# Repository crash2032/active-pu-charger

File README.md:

# Rechargeable Power Board for Active Guitar Pickups

Open-source, rechargeable 9 V supply for active pickups (EMG, Fishman Fluence, Seymour Duncan Blackouts and similar).
It replaces the 9 V battery: a single Li-ion/LiPo cell is charged from USB-C 5 V, boosted, heavily filtered and regulated to a clean **9.0 V**.
The board switches itself on only when a cable is plugged into the guitar (stereo jack, ring contact), and a single bi-color LED shows the charge state — the same behaviour as the Fishman rechargeable pack.

Originally based on the [freestompboxes.org thread](https://www.freestompboxes.org/viewtopic.php?t=32759); **v3** is a full redesign: smaller, lower idle current, all parts on one side, ready for turnkey assembly.

| Top (components) | Bottom |
|---|---|
|  |  |

## Specifications

| | |
|---|---|
| Board | 31 × 19 mm, 2 layers, 1.6 mm, all SMD parts on top |
| Battery | 1 × Li-ion / LiPo (18650, pouch 1200 mAh, …) **with its own protection (BMS)** |
| Charging | TP4057, 5 V from USB-C, 500 mA (Rprog = 2 kΩ) |
| Output | **9.02 V**, regulated, independent of load |
| Output noise | boost → RC (340 Hz) → capacitance multiplier (<1 Hz) → TPS7A4901 ultra-low-noise LDO (15 µV<sub>RMS</sub>, ≥52 dB PSRR to 400 kHz) |
| On/off | automatic via stereo-jack ring (ring = GND when a cable is plugged in) |
| Standby current (cable unplugged) | a few µA (charger leakage + capacitor leakage only) |
| Low-battery warning | red LED blinks below ~3.45 V (≈10–15 % left), blinking gets faster as the cell empties |

### LED indication (D3, one red/green LED)

| State | Red | Green |
|---|---|---|
| Charging | on | – |
| Fully charged | – | on |
| Playing, battery OK | – | – |
| Playing, battery low (< 3.45 V) | **blinking** | – |

## Wiring

All connections are 2.54 mm solder pads (no headers fitted). Labels are printed on the bottom silkscreen.

| Pad | Connect to |
|---|---|
| J3 `5V IN` / `GND` | USB-C charging socket in the guitar (VBUS / GND) |
| J2 `BAT+` / `GND` | battery (+ / −) — the cell **must** have its own BMS |
| J1 `+9V` | pickups / preamp +9 V (replaces the 9 V battery red wire) |
| J1 `GND` | pickups ground / output jack sleeve |
| J1 `RING` | output jack **ring** (stereo jack). Plugging a mono cable shorts ring to sleeve and turns the supply on |

> **USB-C note:** the USB-C socket in the guitar needs 5.1 kΩ pull-downs on CC1 and CC2, otherwise USB-C ↔ USB-C chargers will not supply 5 V.

## How it works

1. **Charger** – TP4057 linear charger (500 mA). STDBY drives the green LED directly (USB-powered); CHRG switches the battery-powered red LED through Q9/Q8, so the charger pins never see battery voltage when USB is unplugged.
2. **Switch-on** – Q7 is turned on by the jack ring; its collector (`VSW`) enables the boost converter and the low-battery detector. R22 holds EN low when unplugged.
3. **Boost** – TPS61041, 11.5 V (R7/R8). Q2 disconnects the output when the boost is off, so nothing drains the cell through the inductor/diode.
4. **Filtering & regulation** – R23/C2 RC filter → Q6 capacitance multiplier (R1/C3) → TPS7A4901 LDO set to 9.02 V by R26/R27 (C21 noise-reduction, C22 feed-forward).
5. **Low-battery blinker** – TLV3012 nanopower comparator with internal 1.242 V reference, wired as a relaxation oscillator that only runs below the threshold (~5 µA, only while a cable is plugged in).

## Repository layout

```
rechargeble_pack.kicad_pro / .kicad_sch / .kicad_pcb   KiCad 9 project
active_pu.kicad_sym, sym-lib-table                     project symbol library (TP4057, TLV3012, TPS7A4901, dual LED)
production/
  active-pu-charger-v3-gerbers.zip                     Gerbers + Excellon drill
  BOM-JLC.csv, CPL-JLC.csv                             JLCPCB assembly (LCSC part numbers)
  BOM-PCBWay.xlsx / .csv, CPL-PCBWay.csv               PCBWay / other turnkey assemblers (manufacturer + MPN)
docs/                                                  preview images
```

## Ordering

1. Upload `production/active-pu-charger-v3-gerbers.zip` (2 layers, 1.6 mm, any finish; min track/space 0.2/0.15 mm, min drill 0.3 mm).
2. For assembly upload the matching BOM + CPL. **Check component rotation in the assembler's placement preview** (SOT-23 and diodes are often offset by 90°/180° between KiCad and the assembler).
3. J1–J3 are wire pads — do not populate.
4. U4 (TPS7A4901) has an exposed thermal pad — it must be soldered (reflow / hot plate).

Before regenerating fabrication files after any edit: open the board in KiCad, press **B** (refill zones) and run **Inspect → Design Rules Checker**.

Notes:
- D3 (Lite-On LTST-C295KGKRKT) has no 3D model in the KiCad library, so it is not shown in the 3D viewer.
- Silkscreen reference designators are kept on the Fab layer (0402 parts are too small for the 1 mm minimum silkscreen text).

## Contacts

Designed by **[Abyss Sound Studio](https://abyss-prod.com/)** — mixing, mastering, video and photo for rock & metal musicians.

- Website: [abyss-prod.com](https://abyss-prod.com/)
- Instagram: [@abyss.sound.studio](https://www.instagram.com/abyss.sound.studio/) (best way to get in touch)
- YouTube: [@AbyssSoundStudio](https://www.youtube.com/@AbyssSoundStudio)
- Facebook: [abyss.sound.studio](https://www.facebook.com/abyss.sound.studio)
- SoundCloud: [abyss-sound-studio](https://soundcloud.com/abyss-sound-studio/sets/our-work)

Questions, bugs and improvements for this board: open an issue or pull request on GitHub.

## Contributing

Contributions are welcome — fork the repo and open a pull request.

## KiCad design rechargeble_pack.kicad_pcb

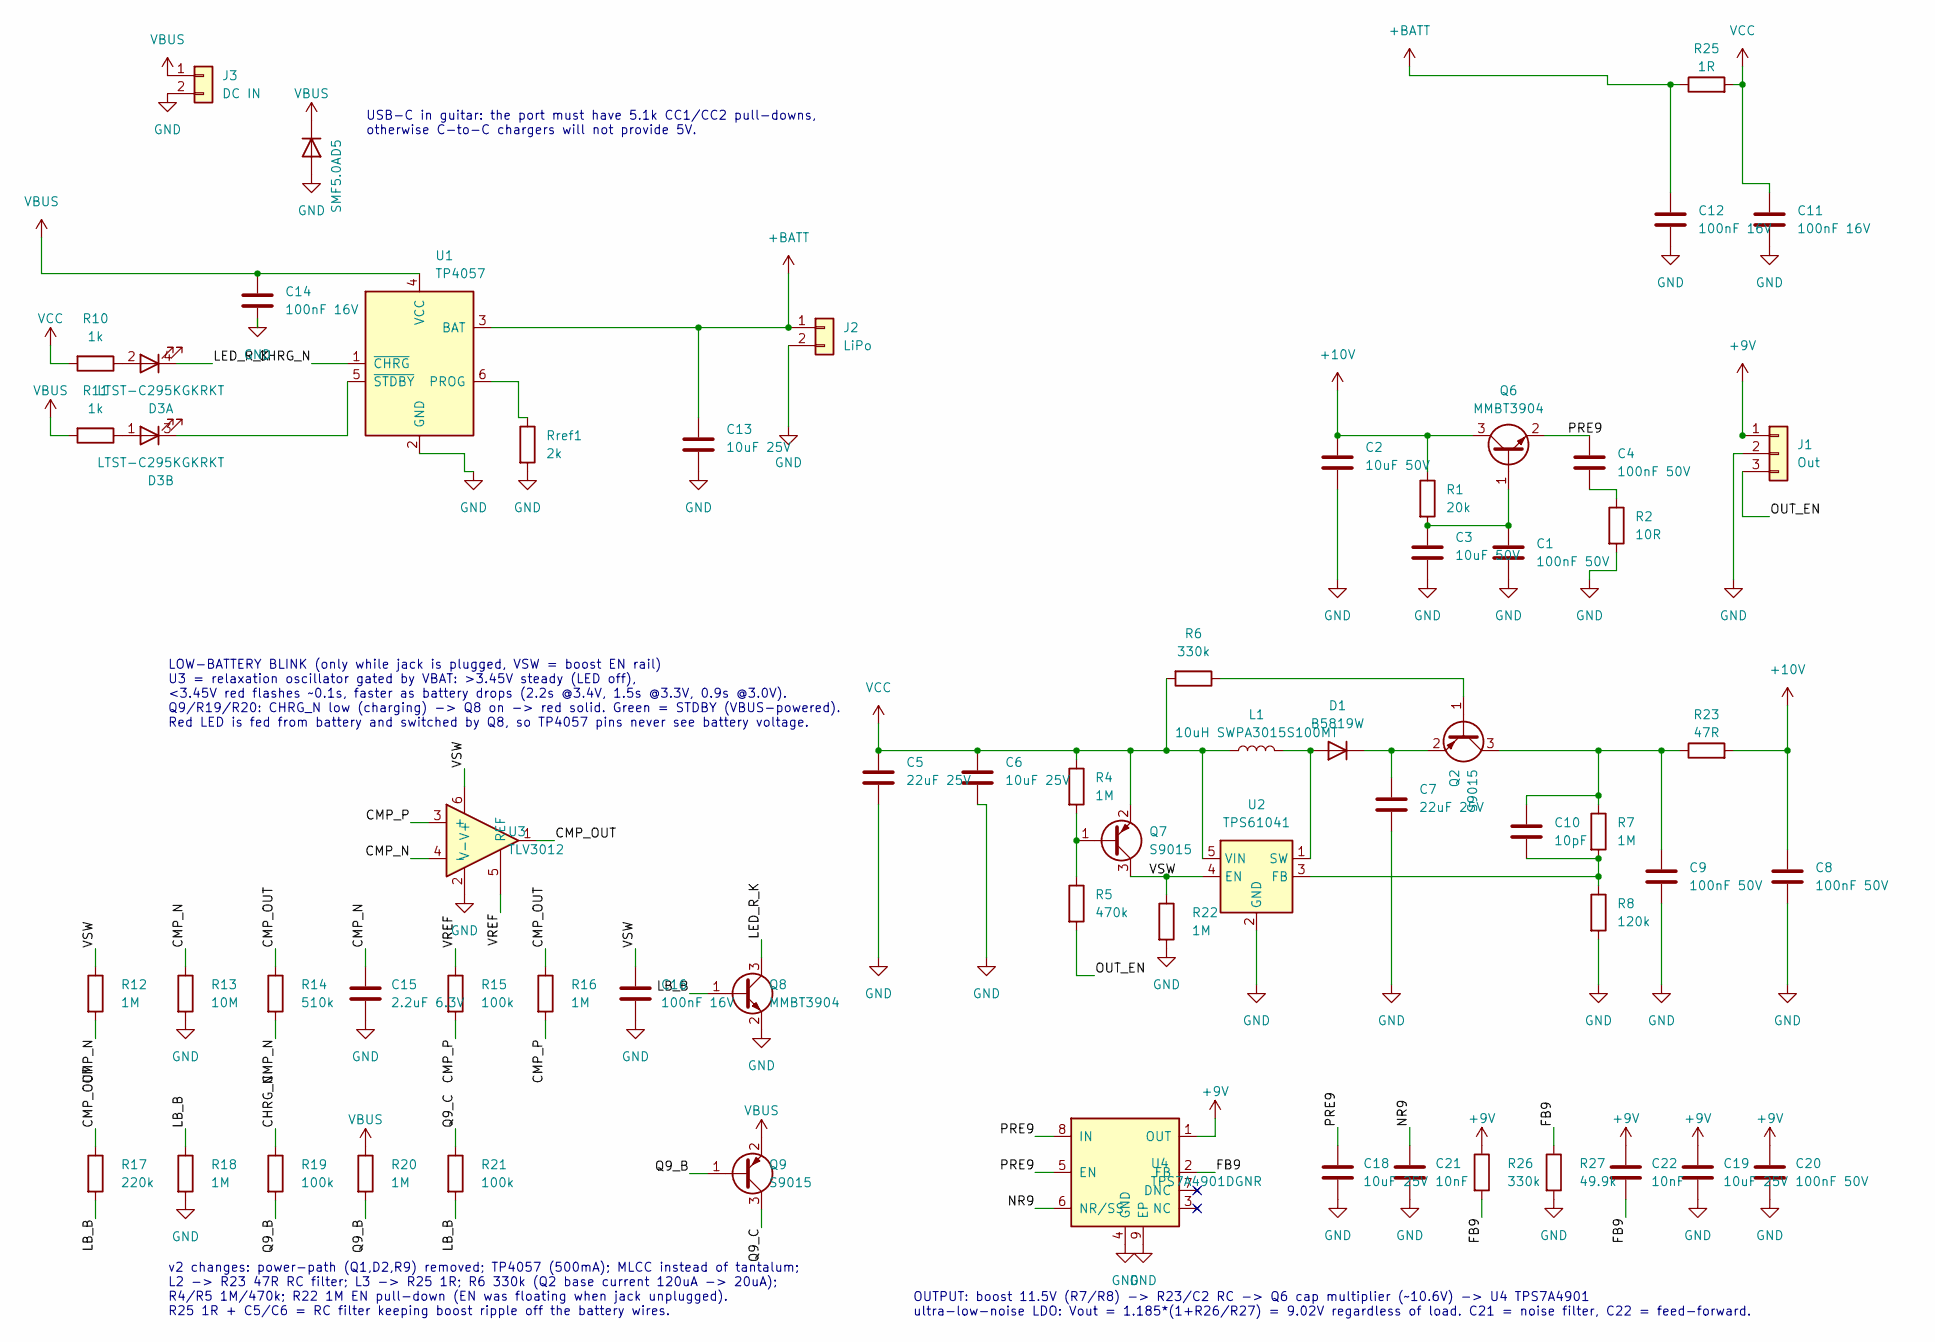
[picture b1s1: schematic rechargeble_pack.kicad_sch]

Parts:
C1, C4, C8, C9, C20: 100nF 50V; C_0402_1005Metric; LCSC C307331
C2, C3: 10uF 50V; C_0805_2012Metric; LCSC C440198
C5: 22uF 25V; C_0805_2012Metric; LCSC C45783
C6, C13, C18, C19: 10uF 25V; C_0805_2012Metric; LCSC C15850
C7: 22uF 25V; C_1206_3216Metric; LCSC C12891
C10: 10pF; C_0402_1005Metric; LCSC C32949
C11, C12, C14, C16: 100nF 16V; C_0402_1005Metric; LCSC C1525
C15: 2.2uF 6.3V; C_0402_1005Metric; LCSC C12530
C21, C22: 10nF; C_0402_1005Metric; LCSC C15195
D1: B5819W; D_SOD-123; LCSC C8598
D3: LTST-C295KGKRKT; LED_LiteOn_LTST-C295K_1.6x0.8mm; LCSC C364568
D5: SMF5.0A; D_SOD-123F; LCSC C193402
J1: Out; PinHeader_1x03_P2.54mm_Vertical
J2: LiPo; PinHeader_1x02_P2.54mm_Vertical
J3: DC IN; PinHeader_1x02_P2.54mm_Vertical
L1: 10uH SWPA3015S100MT; L_Sunlord_SWPA3015S; LCSC C45403
Q2, Q7, Q9: S9015; SOT-23; LCSC C2149
Q6, Q8: MMBT3904; SOT-23; LCSC C20526
R1: 20k; R_0402_1005Metric; LCSC C25765
R2: 10R; R_0402_1005Metric; LCSC C25077
R4, R7, R12, R16, R18, R20, R22: 1M; R_0402_1005Metric; LCSC C26083
R5: 470k; R_0402_1005Metric; LCSC C25790
R6, R26: 330k; R_0402_1005Metric; LCSC C25778
R8: 120k; R_0402_1005Metric; LCSC C25750
R10, R11: 1k; R_0402_1005Metric; LCSC C11702
R13: 10M; R_0402_1005Metric; LCSC C26082
R14: 510k; R_0402_1005Metric; LCSC C11616
R15, R19, R21: 100k; R_0402_1005Metric; LCSC C25741
R17: 220k; R_0402_1005Metric; LCSC C25767
R23: 47R; R_0402_1005Metric; LCSC C25118
R25: 1R; R_0402_1005Metric; LCSC C25086
R27: 49.9k; R_0402_1005Metric; LCSC C25897
Rref1: 2k; R_0402_1005Metric; LCSC C4109
U1: TP4057; SOT-23-6; LCSC C725791
U2: TPS61041; SOT-23-5; LCSC C9846
U3: TLV3012; SOT-23-6; LCSC C62505
U4: TPS7A4901DGNR; Texas_DGN0008D_VSSOP-8-1EP_3x3mm_P0.65mm_EP2x2.94mm_Mask1.5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; LCSC C16430

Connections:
+9V: C19.1, C20.1, C22.1, J1.1, R26.1, U4.1 (OUT)
+10V: C2.1, C8.1, Q6.3 (C), R1.1, R23.2
+BATT: C12.1, C13.1, J2.1, R25.1, U1.3 (BAT)
CHRG_N: R19.1, U1.1 (~CHRG)
CMP_N: C15.1, R12.2, R13.1, R14.2, U3.4 (-)
CMP_OUT: R14.1, R16.1, R17.1, U3.1
CMP_P: R15.2, R16.2, U3.3 (+)
FB9: C22.2, R26.2, R27.1, U4.2 (FB)
GND: C1.2, C2.2, C3.2, C5.2, C6.2, C7.2, C8.2, C9.2, C11.2, C12.2, C13.2, C14.2, C15.2, C16.2, C18.2, C19.2, C20.2, C21.2, D5.2 (A), J1.2, J2.2, J3.2, Q8.2 (E), R2.2, R8.2, R13.2, R18.2, R22.2, R27.2, Rref1.2, U1.2 (GND), U2.2 (GND), U3.2 (V-), U4.4 (GND), U4.9 (EP)
LB_B: Q8.1 (B), R17.2, R18.1, R21.2
LED_R_K: D3.4 (RK), Q8.3 (C)
NR9: C21.1, U4.6 (NR/SS)
unnamed: C1.1, C3.1, Q6.1 (B), R1.2
unnamed: D3.3 (GK), U1.5 (~STDBY)
unnamed: Q2.1 (B), R6.1
unnamed: C7.1, D1.1 (K), Q2.2 (E)
unnamed: C4.2, R2.1
unnamed: Q7.1 (B), R4.2, R5.1
unnamed: C9.1, C10.1, Q2.3 (C), R7.1, R23.1
unnamed: C10.2, R7.2, R8.1, U2.3 (FB)
unnamed: D3.2 (RA), R10.1
unnamed: D3.1 (GA), R11.1
unnamed: Rref1.1, U1.6 (PROG)
unnamed: D1.2 (A), L1.2, U2.1 (SW)
OUT_EN: J1.3, R5.2
PRE9: C4.1, C18.1, Q6.2 (E), U4.5 (EN), U4.8 (IN)
Q9_B: Q9.1 (B), R19.2, R20.2
Q9_C: Q9.3 (C), R21.1
VBUS: C14.1, D5.1 (K), J3.1, Q9.2 (E), R11.2, R20.1, U1.4 (VCC)
VCC: C5.1, C6.1, C11.1, L1.1, Q7.2 (E), R4.1, R6.2, R10.2, R25.2, U2.5 (VIN)
VREF: R15.1, U3.5 (REF)
VSW: C16.1, Q7.3 (C), R12.1, R22.1, U2.4 (EN), U3.6 (V+)

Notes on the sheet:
LOW-BATTERY BLINK (only while jack is plugged, VSW = boost EN rail) U3 = relaxation oscillator gated by VBAT: >3.45V steady (LED off), <3.45V red flashes ~0.1s, faster as battery drops (2.2s @3.4V, 1.5s @3.3V, 0.9s @3.0V). Q9/R19/R20: CHRG_N low (charging) -> Q8 on -> red solid. Green = STDBY (VBUS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
v2 changes: power-path (Q1,D2,R9) removed; TP4057 (500mA); MLCC instead of tantalum; L2 -> R23 47R RC filter; L3 -> R25 1R; R6 330k (Q2 base current 120uA -> 20uA); R4/R5 1M/470k; R22 1M EN pull-down (EN was floating when jack unplugged). R25 1R + C5/C6 = RC filter keeping boost ripple off the batt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
USB-C in guitar: the port must have 5.1k CC1/CC2 pull-downs, otherwise C-to-C chargers will not provide 5V.
OUTPUT: boost 11.5V (R7/R8) -> R23/C2 RC -> Q6 cap multiplier (~10.6V) -> U4 TPS7A4901 ultra-low-noise LDO: Vout = 1.185*(1+R26/R27) = 9.02V regardless of load. C21 = noise filter, C22 = feed-forward.

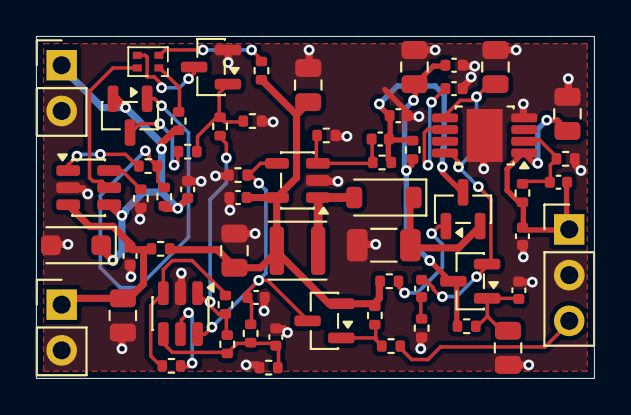
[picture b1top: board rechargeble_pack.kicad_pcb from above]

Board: 2 copper layers, 31.0 x 19.0 mm, 62 parts (0 on the bottom side), 32 nets.

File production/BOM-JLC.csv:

Comment,Designator,Footprint,LCSC Part #
10pF,C10,C_0402_1005Metric,C32949
10uF 25V,"C6,C13,C18,C19",C_0805_2012Metric,C15850
100nF 16V,"C11,C12,C14,C16",C_0402_1005Metric,C1525
2.2uF 6.3V,C15,C_0402_1005Metric,C12530
10uF 50V,"C2,C3",C_0805_2012Metric,C440198
10nF,"C21,C22",C_0402_1005Metric,C15195
22uF 25V,C5,C_0805_2012Metric,C45783
22uF 25V,C7,C_1206_3216Metric,C12891
100nF 50V,"C1,C4,C8,C9,C20",C_0402_1005Metric,C307331
B5819W,D1,D_SOD-123,C8598
LTST-C295KGKRKT,D3,LED_LiteOn_LTST-C295K_1.6x0.8mm,C364568
SMF5.0A,D5,D_SOD-123F,C193402
10uH SWPA3015S100MT,L1,L_Sunlord_SWPA3015S,C45403
S9015,"Q2,Q7,Q9",SOT-23,C2149
MMBT3904,"Q6,Q8",SOT-23,C20526
20k,R1,R_0402_1005Metric,C25765
1k,"R10,R11",R_0402_1005Metric,C11702
10M,R13,R_0402_1005Metric,C26082
510k,R14,R_0402_1005Metric,C11616
100k,"R15,R19,R21",R_0402_1005Metric,C25741
220k,R17,R_0402_1005Metric,C25767
10R,R2,R_0402_1005Metric,C25077
47R,R23,R_0402_1005Metric,C25118
1R,R25,R_0402_1005Metric,C25086
49.9k,R27,R_0402_1005Metric,C25897
470k,R5,R_0402_1005Metric,C25790
330k,"R6,R26",R_0402_1005Metric,C25778
1M,"R4,R7,R12,R16,R18,R20,R22",R_0402_1005Metric,C26083
120k,R8,R_0402_1005Metric,C25750
2k,Rref1,R_0402_1005Metric,C4109
TP4057,U1,SOT-23-6,C725791
TPS61041,U2,SOT-23-5,C9846
TLV3012,U3,SOT-23-6,C62505
TPS7A4901DGNR,U4,Texas_DGN0008D_VSSOP-8-1EP_3x3mm_P0.65mm_EP2x2.94mm_Mask1.57x1.89mm,C16430

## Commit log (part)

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2025-07-04 added kicad files
2025-07-07 Schematics fix
    Schematics values fix
2025-07-08 gerber-ready
    gerber+bom
2025-07-08 fix
    ...
2025-07-09 need fix
2025-07-09 final
2025-07-10 fix mosfet
2025-10-22 gnd polygon
